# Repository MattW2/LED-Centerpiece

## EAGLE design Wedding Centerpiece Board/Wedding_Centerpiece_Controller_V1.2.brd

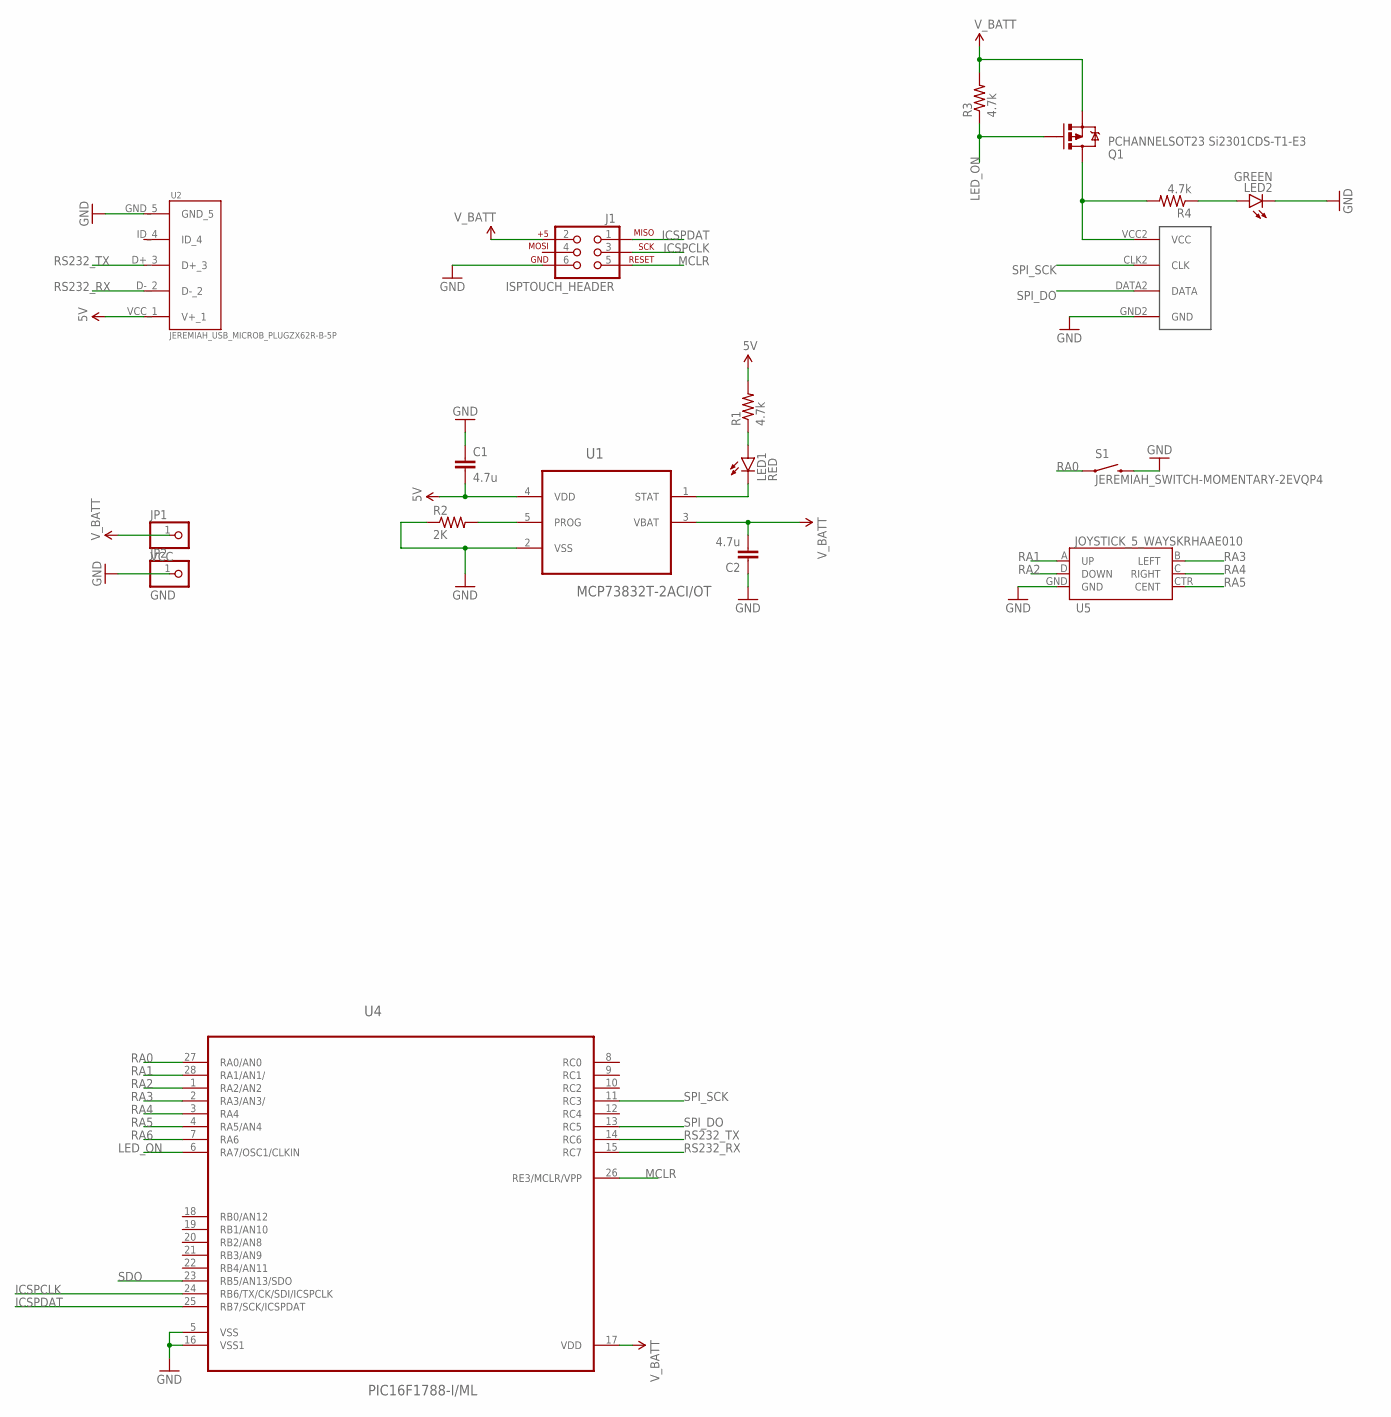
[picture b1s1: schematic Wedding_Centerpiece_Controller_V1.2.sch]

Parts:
C1, C2: 4.7u; 0402-CAP
J1: ISPTOUCH_HEADER; AVX_9188_6-WAY_MATING_GUIDE
JP1: VCC; 1X01
JP2: GND; 1X01
LED1: RED; LED-0603
LED2: GREEN; LED-0603
Q1: PCHANNELSOT23 Si2301CDS-T1-E3; JEREMIAH_SOT23
R1, R3, R4: 4.7k; R0402
R2: 2K; R0402
S1: JEREMIAH_SWITCH-MOMENTARY-2EVQP4; JEREMIAH_EVQP4_SWITCH
U1: MCP73832T-2ACI/OT; SOT95P280X145-5N
U2: JEREMIAH_USB_MICROB_PLUGZX62R-B-5P; JEREMIAH_USB_MICRO_ZX62R-B-5P
U3: JEREMIAH_LED_STRIP_WS2801CLENLED_2L_BEGIN; JEREMIAH_LED_STRIP_WS2801_CLENLED_2L_BEGIN
U4: PIC16F1788-I/ML; QFN65P600X600X100-29N
U5: JOYSTICK_5_WAYSKRHAAE010; ALPS_SKRHAAE010

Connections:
5V: C1.2, R1.2, U1.4 (VDD), U2.VCC_1 (V+_1)
GND: C1.1, C2.1, J1.6, JP2.1, LED2.C, R2.1, S1.2, U1.2 (VSS), U2.GND_5, U3.GND2 (GND), U4.5 (VSS), U4.16 (VSS1), U5.GND
ICSPCLK: J1.3, U4.24 (RB6/TX/CK/SDI/ICSPCLK)
ICSPDAT: J1.1, U4.25 (RB7/SCK/ICSPDAT)
LED_ON: Q1.1 (G), R3.1, U4.6 (RA7/OSC1/CLKIN)
MCLR: J1.5, U4.26 (RE3/MCLR/VPP)
unnamed: R2.2, U1.5 (PROG)
unnamed: LED1.A, R1.1
unnamed: LED1.C, U1.1 (STAT)
unnamed: Q1.3 (D), R4.2, U3.VCC2 (VCC)
unnamed: LED2.A, R4.1
RA0: S1.1, U4.27 (RA0/AN0)
RA1: U4.28 (RA1/AN1/), U5.A (UP)
RA2: U4.1 (RA2/AN2), U5.D (DOWN)
RA3: U4.2 (RA3/AN3/), U5.B (LEFT)
RA4: U4.3 (RA4), U5.C (RIGHT)
RA5: U4.4 (RA5/AN4), U5.CTR (CENT)
RA6: U4.7 (RA6)
RS232_RX: U2.D-_2, U4.15 (RC7)
RS232_TX: U2.D+_3, U4.14 (RC6)
SDO: U4.23 (RB5/AN13/SDO)
SPI_DO: U3.DATA2 (DATA), U4.13 (RC5)
SPI_SCK: U3.CLK2 (CLK), U4.11 (RC3)
V_BATT: C2.2, J1.2, JP1.1, Q1.2 (S), R3.2, U1.3 (VBAT), U4.17 (VDD)

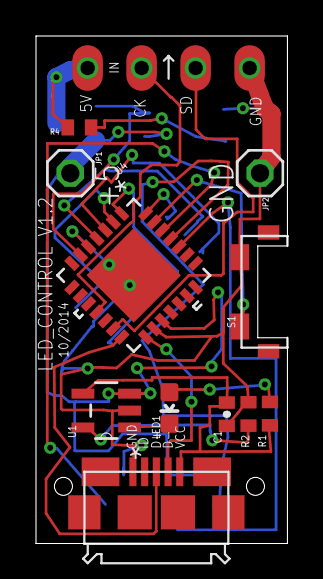
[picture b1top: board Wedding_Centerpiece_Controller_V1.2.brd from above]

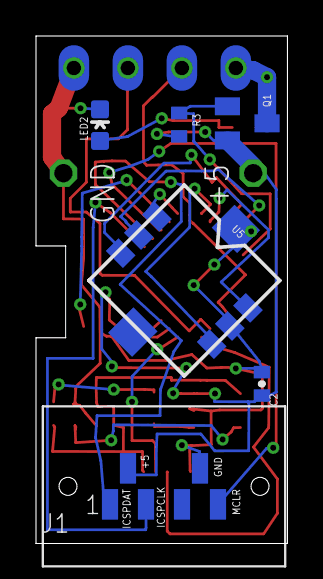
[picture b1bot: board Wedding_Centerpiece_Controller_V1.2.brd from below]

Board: 2 copper layers, 14.0 x 28.2 mm, 18 parts (6 on the bottom side), 22 nets.

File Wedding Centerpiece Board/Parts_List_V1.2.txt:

Partlist

Exported from Wedding_Centerpiece_Controller_V1.2.sch at 11/7/2014 6:28:05 PM

EAGLE Version 6.4.0 Copyright (c) 1988-2013 CadSoft

Assembly variant: 

Part     Value                                     Device                                    Package                                    Library                          Sheet

C1       4.7u                                      CAP0402-CAP                               0402-CAP                                   SparkFun-Passives                1
C2       4.7u                                      CAP0402-CAP                               0402-CAP                                   SparkFun-Passives                1
J1       ISPTOUCH_HEADER                           ISPTOUCH_HEADER                           AVX_9188_6-WAY_MATING_GUIDE                daspilker                        1
JP1      VCC                                       PINHD-1X1                                 1X01                                       pinhead                          1
JP2      GND                                       PINHD-1X1                                 1X01                                       pinhead                          1
LED1     RED                                       LED0603                                   LED-0603                                   SparkFun-LED                     1
LED2     GREEN                                     LED0603                                   LED-0603                                   SparkFun-LED                     1
Q1       PCHANNELSOT23 Si2301CDS-T1-E3             JEREMIAH_MOSFET-PCHANNELSOT23             JEREMIAH_SOT23                             Phoenix_Hoop_94_PolyPro_AlwaysOn 1
R1       4.7k                                      R-US_R0402                                R0402                                      resistor                         1
R2       2K                                        R-US_R0402                                R0402                                      resistor                         1
R3       4.7k                                      R-US_R0402                                R0402                                      resistor                         1
R4       4.7k                                      R-US_R0402                                R0402                                      resistor                         1
S1       JEREMIAH_SWITCH-MOMENTARY-2EVQP4          JEREMIAH_SWITCH-MOMENTARY-2EVQP4          JEREMIAH_EVQP4_SWITCH                      Phoenix_Hoop_94_PolyPro_AlwaysOn 1
U1       MCP73832T-2ACI/OT                         MCP73832T-2ACI/OT                         SOT95P280X145-5N                           Microchip_By_element14_Batch_1   1
U2       JEREMIAH_USB_MICROB_PLUGZX62R-B-5P        JEREMIAH_USB_MICROB_PLUGZX62R-B-5P        JEREMIAH_USB_MICRO_ZX62R-B-5P              Phoenix_Hoop_94_PolyPro_AlwaysOn 1
U3       JEREMIAH_LED_STRIP_WS2801CLENLED_2L_BEGIN JEREMIAH_LED_STRIP_WS2801CLENLED_2L_BEGIN JEREMIAH_LED_STRIP_WS2801_CLENLED_2L_BEGIN Phoenix_Hoop_94_PolyPro_AlwaysOn 1
U4       PIC16F1788-I/ML                           PIC16F1788-I/ML                           QFN65P600X600X100-29N                      Microchip                        1
U5       JOYSTICK_5_WAYSKRHAAE010                  JOYSTICK_5_WAYSKRHAAE010                  ALPS_SKRHAAE010                            Switches                         1

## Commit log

2015-12-03 First Commit of files

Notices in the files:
parts and their libraries:
SparkFun-LED: Licensing: Creative Commons ShareAlike 4.0 International - https://creativecommons.org/licenses/by-sa/4.0
